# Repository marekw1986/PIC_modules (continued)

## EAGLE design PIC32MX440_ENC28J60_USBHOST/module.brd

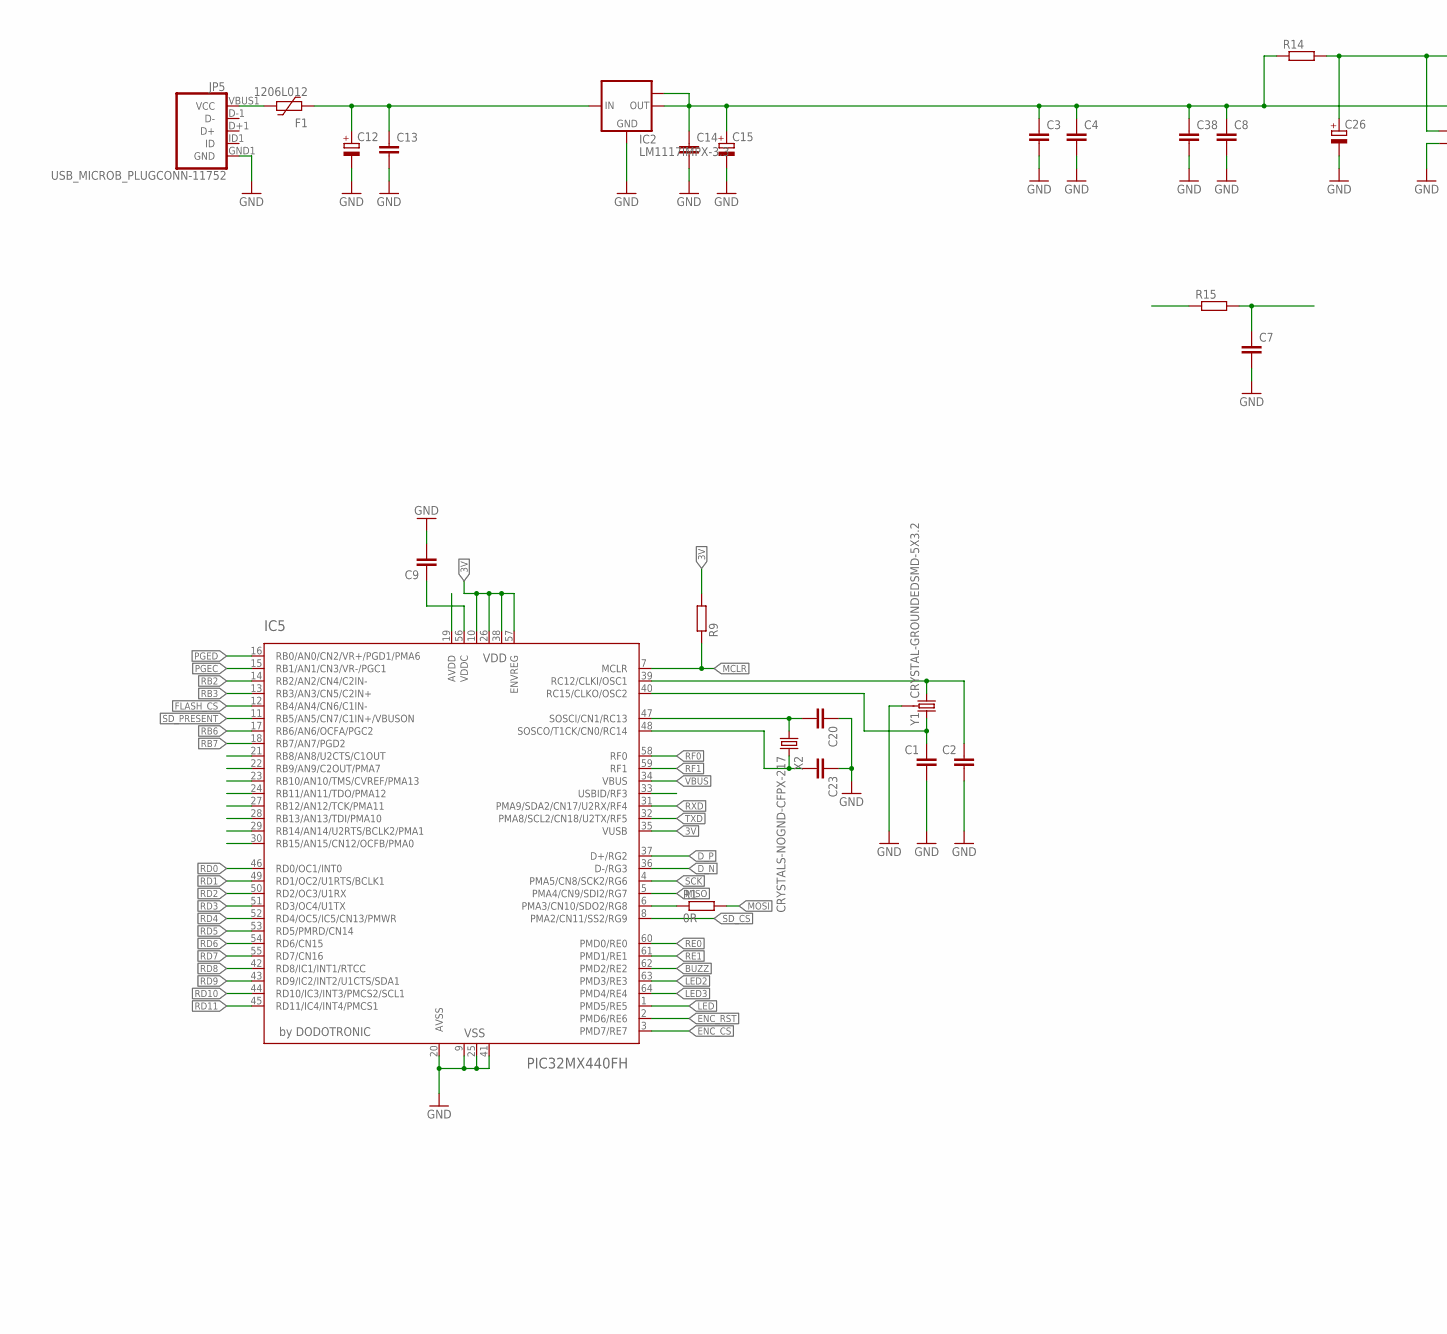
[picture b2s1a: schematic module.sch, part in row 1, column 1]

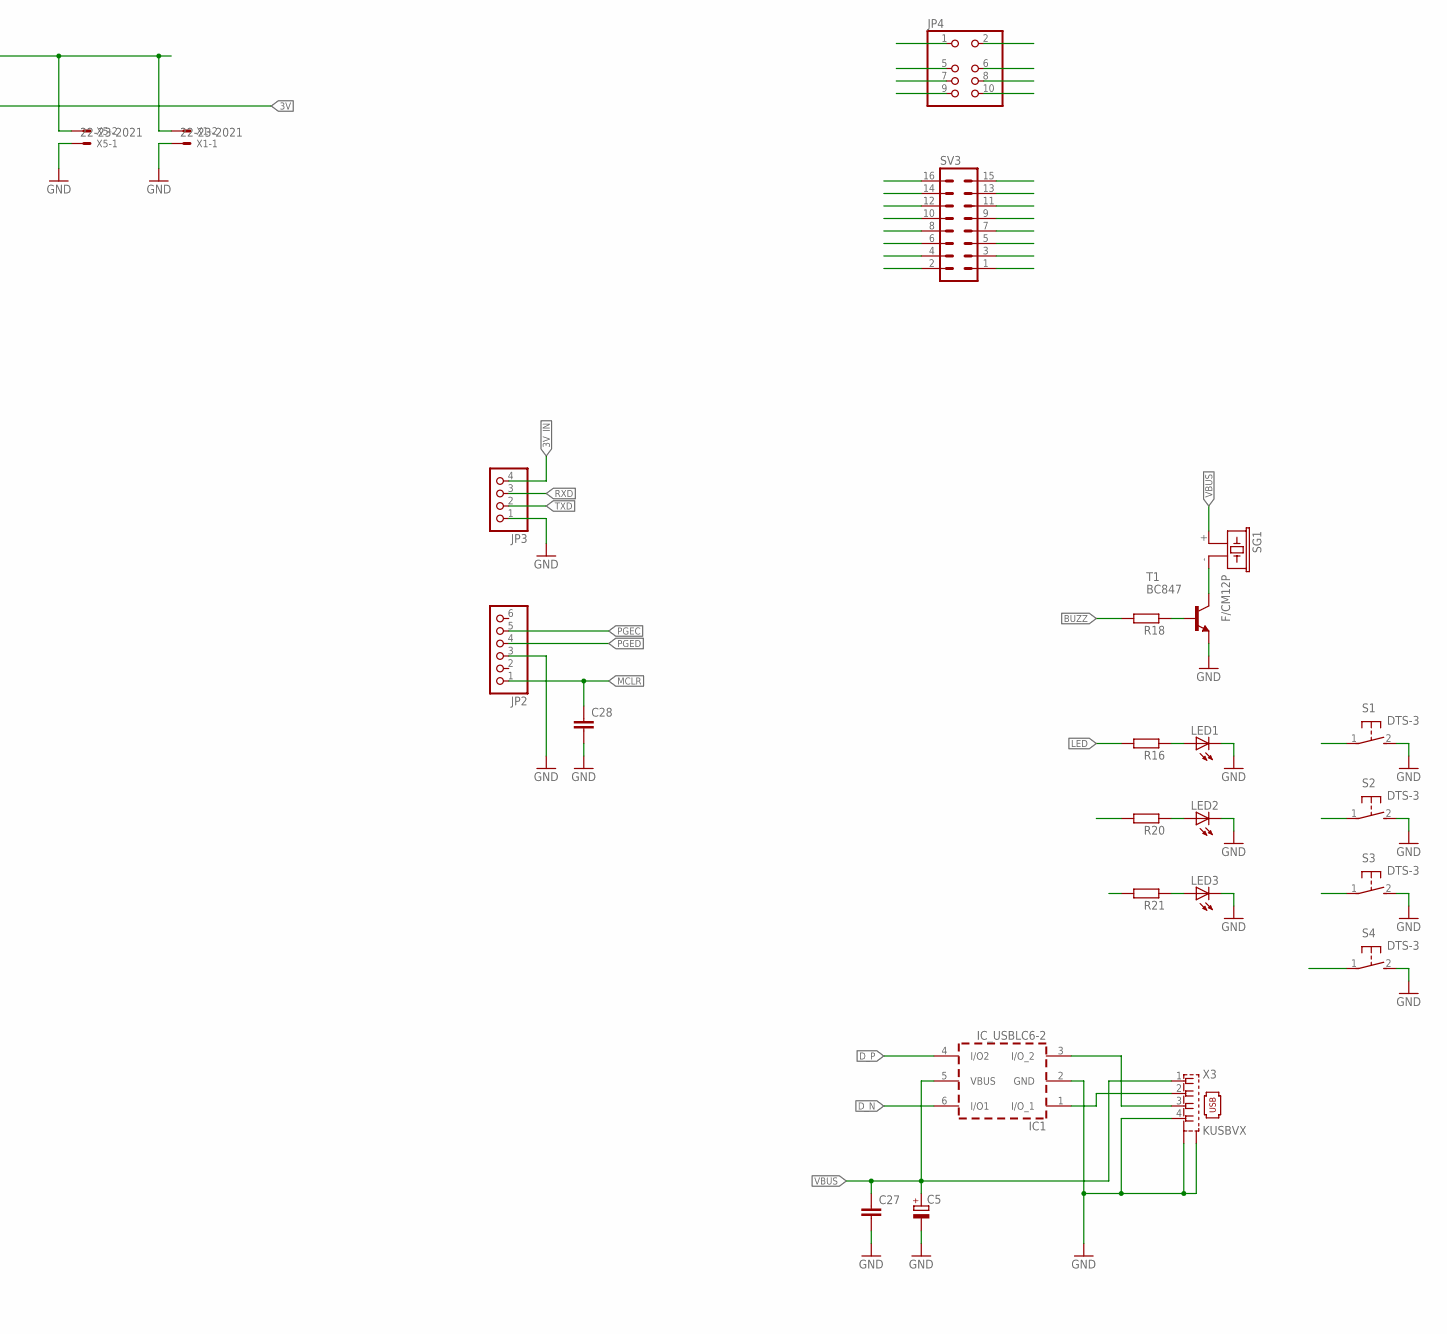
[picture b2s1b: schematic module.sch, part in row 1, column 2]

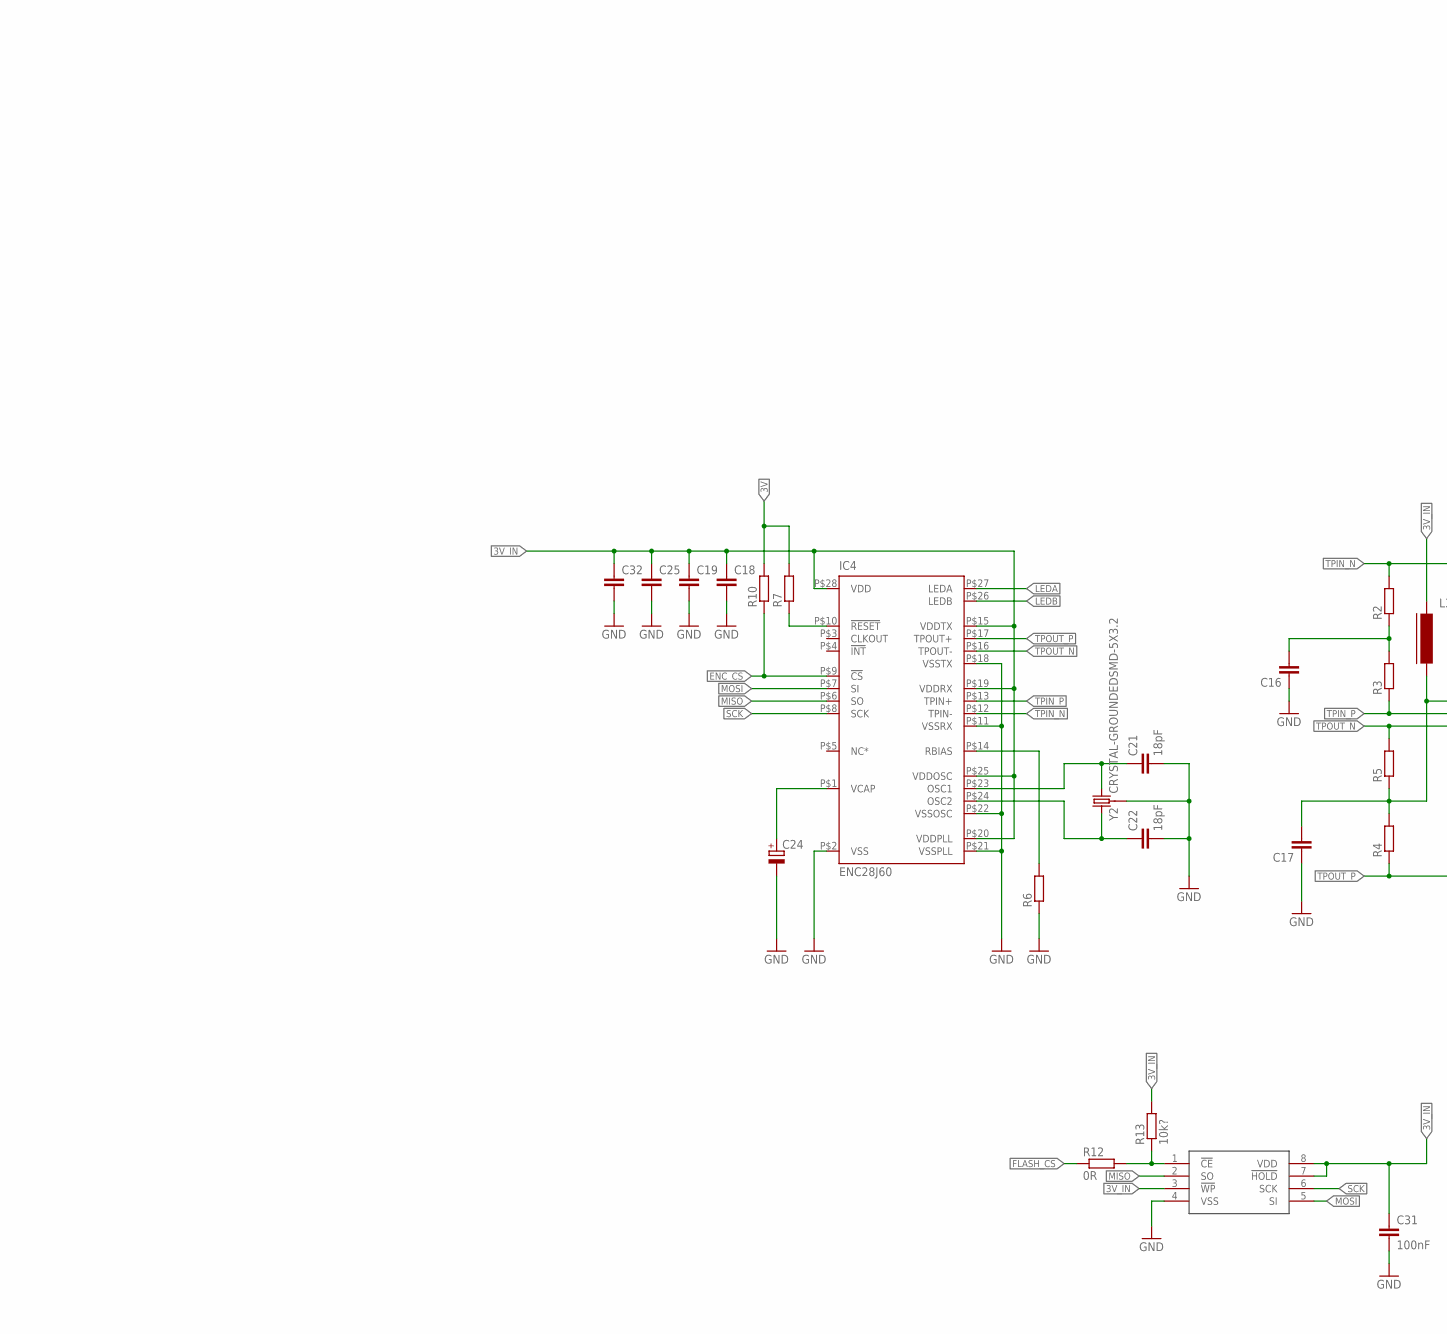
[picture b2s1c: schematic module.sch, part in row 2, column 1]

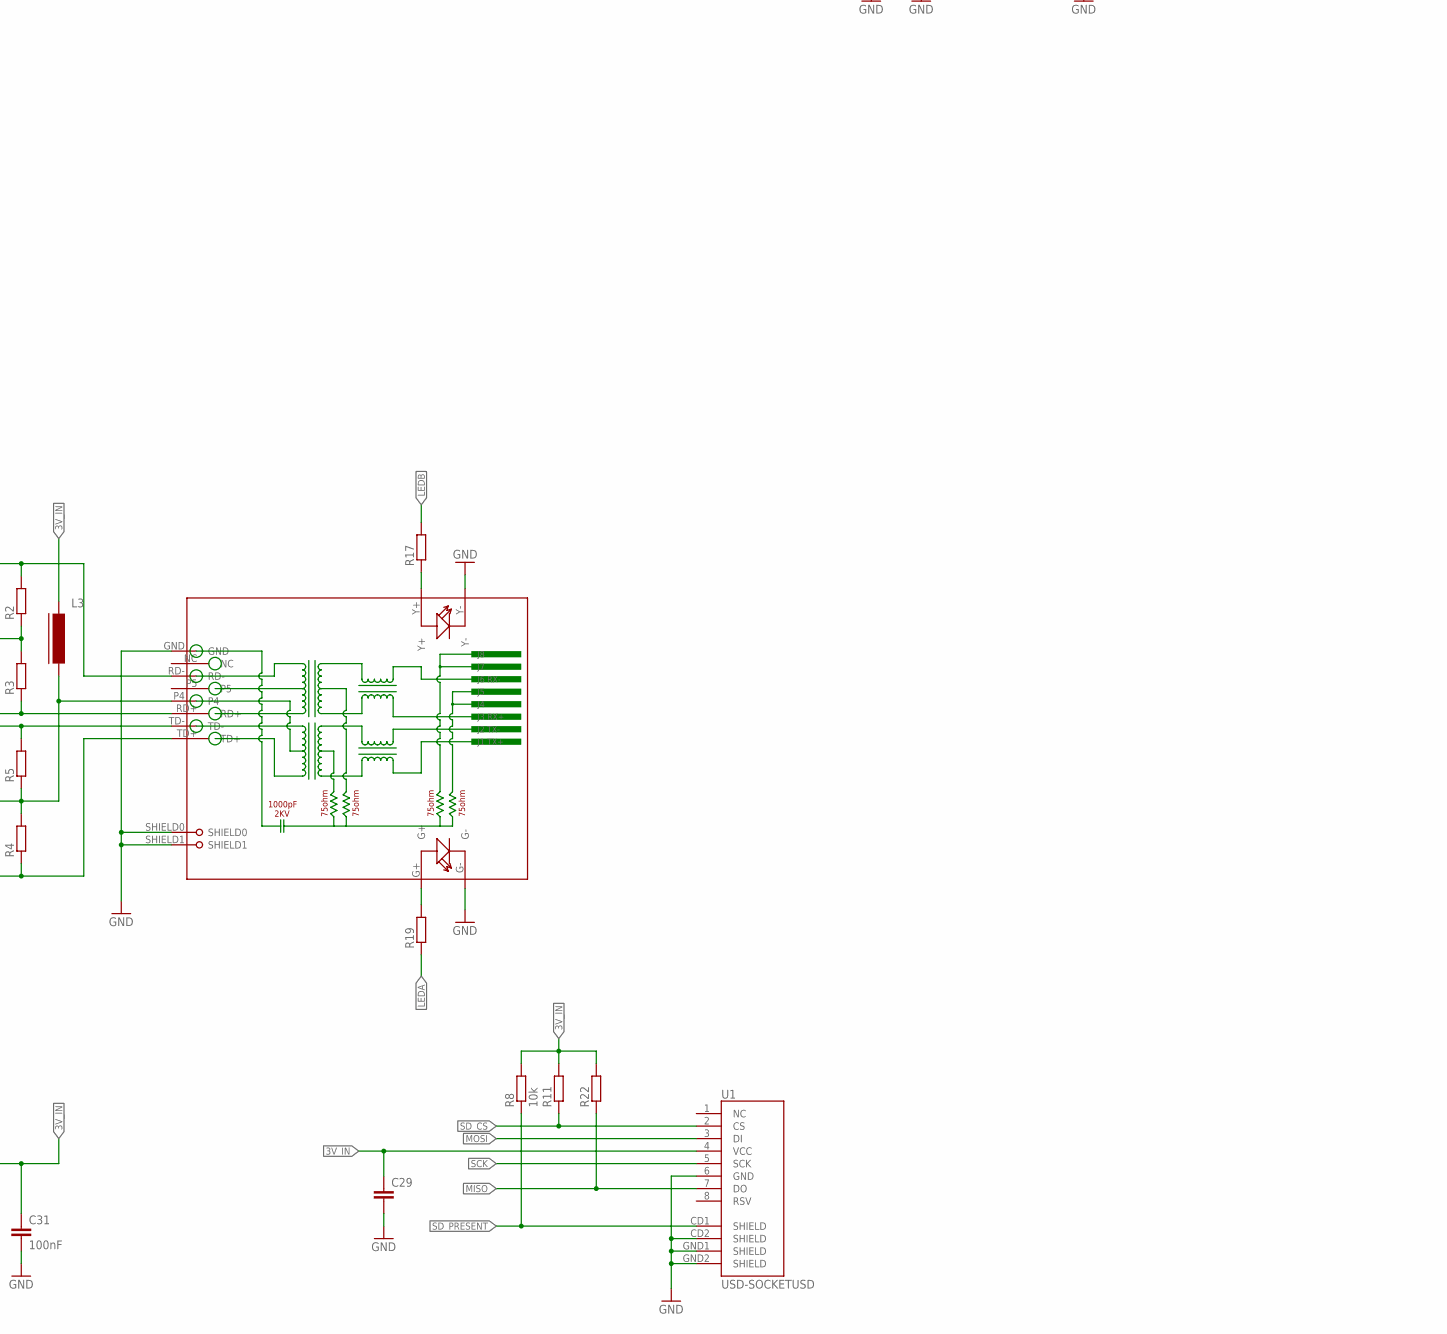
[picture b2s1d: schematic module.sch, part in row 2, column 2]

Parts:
C1, C2, C9, C13, C14, C16, C17, C19, C20, C23, C25, C27, C28, C29, C38: C-EUC0603; C0603
C3, C4, C7, C8, C18, C32: C-EUC0402; C0402
C5, C24, C26: CPOL-EUSMCA; SMC_A
C12, C15: CPOL-EUSMCB; SMC_B
C21, C22: 18pF; C0603
C31: 100nF; C0603
F1: 1206L012; 1206L
IC1: IC_USBLC6-2; SOT-23-6L
IC2: LM1117IMPX-3.3; SOT223
IC4: ENC28J60; TSSOP28W
IC5: PIC32MX440FH; TQFP64-10X10
JP2: PINHD-1X6; 1X06
JP3: PINHD-1X4; 1X04
JP4: PINHD-2X5; 2X05
JP5: USB_MICROB_PLUGCONN-11752; USB-B-MICRO-SMD_V03
L3: FERRITE-0805; FB805
LED1, LED2, LED3: LED3MM
R1, R12: 0R; R0603
R2, R3, R4, R5, R9, R10, R11, R16, R18, R20, R21, R22: R-EU_R0603; R0603
R6, R15: R-EU_R0805; R0805
R7: R-EU_R0402; R0402
R8: 10k; R0603
R13: 10k?; R0603
R14: R-EU_R2010; R2010
R17, R19: R-EU_R1206; R1206
RJ1: HR911105A
S1, S2, S3, S4: DTS-3
SG1: F/CM12P
SV3: ML16L
T1: BC847; SOT23
U1: USD-SOCKETUSD; USD-SOCKET-PP
U$2: SST25VF016BSO8M; SO-08M
X1, X5: 22-23-2021
X2: CRYSTALS-NOGND-CFPX-217; 3.2X1.5-2-PAD
X3: KUSBVX
Y1, Y2: CRYSTAL-GROUNDEDSMD-5X3.2; CRYSTAL-SMD-5X3.2-4PAD

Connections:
3V: C3.1, C4.1, C8.1, C14.1, C15.+, C38.1, IC2.2 (OUT), IC2.TAB (OUT1), IC5.10 (VDD), IC5.26 (VDD), IC5.35 (VUSB), IC5.38 (VDD), IC5.57 (ENVREG), R7.2, R9.2, R10.2, R14.1
3V_IN: C18.1, C19.1, C25.1, C26.+, C29.1, C31.1, C32.1, IC4.P$15 (VDDTX), IC4.P$19 (VDDRX), IC4.P$20 (VDDPLL), IC4.P$25 (VDDOSC), IC4.P$28 (VDD), JP3.4, L3.1, R8.2, R11.2, R13.2, R14.2, R15.1, R22.2, U1.4 (VCC), U$2.3 (!WP), U$2.7 (!HOLD), U$2.8 (VDD), X1.2, X5.2
AV_3V: C7.1, IC5.19 (AVDD), R15.2
BUZZ: IC5.62 (PMD2/RE2), R18.2
CE1: R12.2, R13.1, U$2.1 (!CE)
D2_N: IC1.1 (I/O_1), X3.2
D2_P: IC1.3 (I/O_2), X3.3
D_N: IC1.6 (I/O1), IC5.36 (D-/RG3)
D_P: IC1.4 (I/O2), IC5.37 (D+/RG2)
ENC_CS: IC4.P$9 (!CS), IC5.3 (PMD7/RE7), R10.1
ENC_RST: IC4.P$10 (!RESET), IC5.2 (PMD6/RE6), R7.1
FLASH_CS: IC5.12 (RB4/AN4/CN6/C1IN-), R12.1
GND: C1.2, C2.2, C3.2, C4.2, C5.-, C7.2, C8.2, C9.2, C12.-, C13.2, C14.2, C15.-, C16.1, C17.1, C18.2, C19.2, C20.1, C21.2, C22.2, C23.1, C24.-, C25.2, C26.-, C27.2, C28.2, C29.2, C31.2, C32.2, C38.2, IC1.2 (GND), IC2.1 (GND), IC4.P$2 (VSS), IC4.P$11 (VSSRX), IC4.P$18 (VSSTX), IC4.P$21 (VSSPLL), IC4.P$22 (VSSOSC), IC5.9 (VSS), IC5.20 (AVSS), IC5.25 (VSS), IC5.41 (VSS), JP2.3, JP3.1, JP5.GND1 (GND), LED1.K (C), LED2.K (C), LED3.K (C), R6.1, RJ1.G-, RJ1.GND, RJ1.SHIELD0, RJ1.SHIELD1, RJ1.Y-, S1.2, S2.2, S3.2, S4.2, T1.2 (E), U1.6 (GND), U1.CD2 (SHIELD), U1.GND1 (SHIELD), U1.GND2 (SHIELD), U$2.4 (VSS), X1.1, X3.4, X3.M1 (S1), X3.M2 (S2), X5.1, Y1.2 (3), Y1.4 (3), Y2.2 (3), Y2.4 (3)
LED: IC5.1 (PMD5/RE5), R16.2
LED2: IC5.63 (PMD3/RE3), R20.2
LED3: IC5.64 (PMD4/RE4), R21.2
LEDA: IC4.P$27 (LEDA), R19.1
LEDB: IC4.P$26 (LEDB), R17.2
MCLR: C28.1, IC5.7 (MCLR), JP2.1, R9.1
MISO: IC4.P$6 (SO), IC5.5 (PMA4/CN9/SDI2/RG7), R22.1, U1.7 (DO), U$2.2 (SO)
MOSI: IC4.P$7 (SI), R1.2, U1.3 (DI), U$2.5 (SI)
unnamed: SG1.- (2), T1.3 (C)
unnamed: C16.2, R2.1, R3.2
unnamed: R18.1, T1.1 (B)
unnamed: LED1.A, R16.1
unnamed: IC5.6 (PMA3/CN10/SDO2/RG8), R1.1
unnamed: C17.2, L3.2, R4.2, R5.1, RJ1.P4
unnamed: LED2.A, R20.1
unnamed: IC4.P$14 (RBIAS), R6.2
unnamed: LED3.A, R21.1
unnamed: IC5.21 (RB8/AN8/U2CTS/C1OUT), JP4.9
unnamed: IC5.22 (RB9/AN9/C2OUT/PMA7), JP4.10
unnamed: IC5.23 (RB10/AN10/TMS/CVREF/PMA13), JP4.7
unnamed: F1.1, JP5.VBUS1 (VCC)
unnamed: IC5.24 (RB11/AN11/TDO/PMA12), JP4.8
unnamed: IC5.28 (RB13/AN13/TDI/PMA10), JP4.5
unnamed: IC5.29 (RB14/AN14/U2RTS/BCLK2/PMA1), JP4.6
unnamed: C21.1, IC4.P$23 (OSC1), Y2.1 (2)
unnamed: C22.1, IC4.P$24 (OSC2), Y2.3 (1)
unnamed: IC5.30 (RB15/AN15/CN12/OCFB/PMA0), JP4.1
unnamed: IC5.33 (USBID/RF3), JP4.2
unnamed: C24.+, IC4.P$1 (VCAP)
unnamed: R17.1, RJ1.Y+
unnamed: R19.2, RJ1.G+
OSC1: C2.1, IC5.39 (RC12/CLKI/OSC1), Y1.1 (2)
OSC2: C1.1, IC5.40 (RC15/CLKO/OSC2), Y1.3 (1)
PGEC: IC5.15 (RB1/AN1/CN3/VR-/PGC1), JP2.5
PGED: IC5.16 (RB0/AN0/CN2/VR+/PGD1/PMA6), JP2.4
RB2: IC5.14 (RB2/AN2/CN4/C2IN-), S2.1
RB3: IC5.13 (RB3/AN3/CN5/C2IN+), S1.1
RB6: IC5.17 (RB6/AN6/OCFA/PGC2), S3.1
RB7: IC5.18 (RB7/AN7/PGD2), S4.1
RD0: IC5.46 (RD0/OC1/INT0), SV3.6
RD1: IC5.49 (RD1/OC2/U1RTS/BCLK1), SV3.5
RD2: IC5.50 (RD2/OC3/U1RX), SV3.8
RD3: IC5.51 (RD3/OC4/U1TX), SV3.7
RD4: IC5.52 (RD4/OC5/IC5/CN13/PMWR), SV3.10
RD5: IC5.53 (RD5/PMRD/CN14), SV3.9
RD6: IC5.54 (RD6/CN15), SV3.12
RD7: IC5.55 (RD7/CN16), SV3.11
RD8: IC5.42 (RD8/IC1/INT1/RTCC), SV3.2
RD9: IC5.43 (RD9/IC2/INT2/U1CTS/SDA1), SV3.1
RD10: IC5.44 (RD10/IC3/INT3/PMCS2/SCL1), SV3.4
RD11: IC5.45 (RD11/IC4/INT4/PMCS1), SV3.3
RE0: IC5.60 (PMD0/RE0), SV3.16
RE1: IC5.61 (PMD1/RE1), SV3.15
RF0: IC5.58 (RF0), SV3.14
RF1: IC5.59 (RF1), SV3.13
RXD: IC5.31 (PMA9/SDA2/CN17/U2RX/RF4), JP3.3
SCK: IC4.P$8 (SCK), IC5.4 (PMA5/CN8/SCK2/RG6), U1.5 (SCK), U$2.6 (SCK)
SD_CS: IC5.8 (PMA2/CN11/SS2/RG9), R11.1, U1.2 (CS)
SD_PRESENT: IC5.11 (RB5/AN5/CN7/C1IN+/VBUSON), R8.1, U1.CD1 (SHIELD)
SOSCI: C20.2, IC5.47 (SOSCI/CN1/RC13), X2.1
SOSCO: C23.2, IC5.48 (SOSCO/T1CK/CN0/RC14), X2.2
TPIN_N: IC4.P$12 (TPIN-), R2.2, RJ1.RD-
TPIN_P: IC4.P$13 (TPIN+), R3.1, RJ1.RD+
TPOUT_N: IC4.P$16 (TPOUT-), R5.2, RJ1.TD-
TPOUT_P: IC4.P$17 (TPOUT+), R4.1, RJ1.TD+
TXD: IC5.32 (PMA8/SCL2/CN18/U2TX/RF5), JP3.2
VBUS: C5.+, C12.+, C13.1, C27.1, F1.2, IC1.5 (VBUS), IC2.3 (IN), IC5.34 (VBUS), SG1.+ (1), X3.1
VCAP: C9.1, IC5.56 (VDDC)

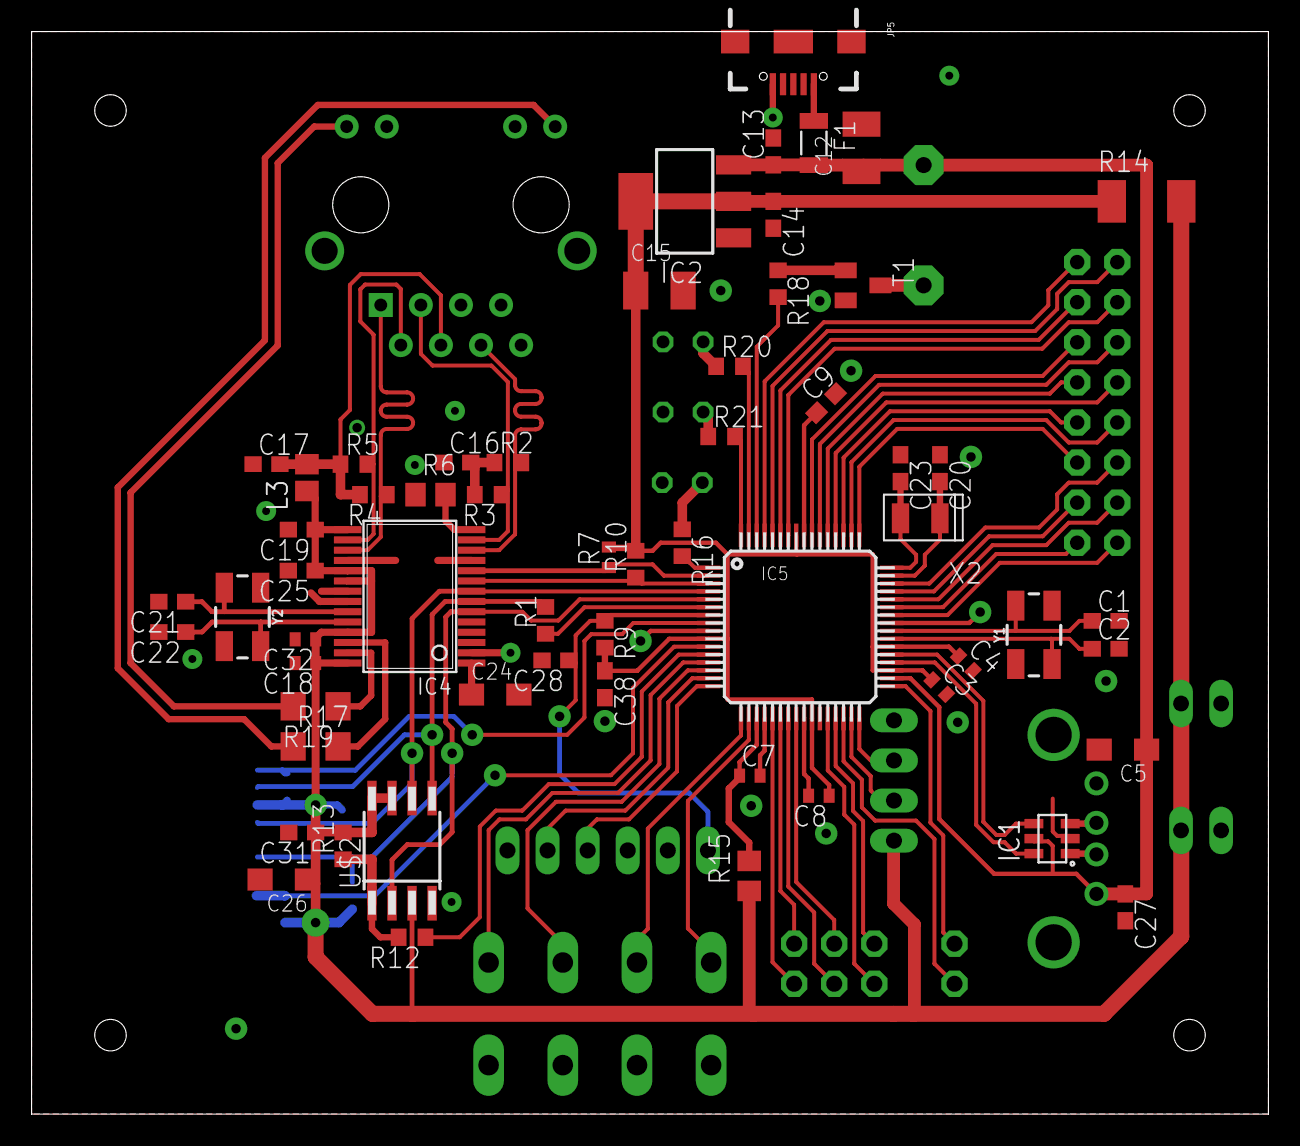
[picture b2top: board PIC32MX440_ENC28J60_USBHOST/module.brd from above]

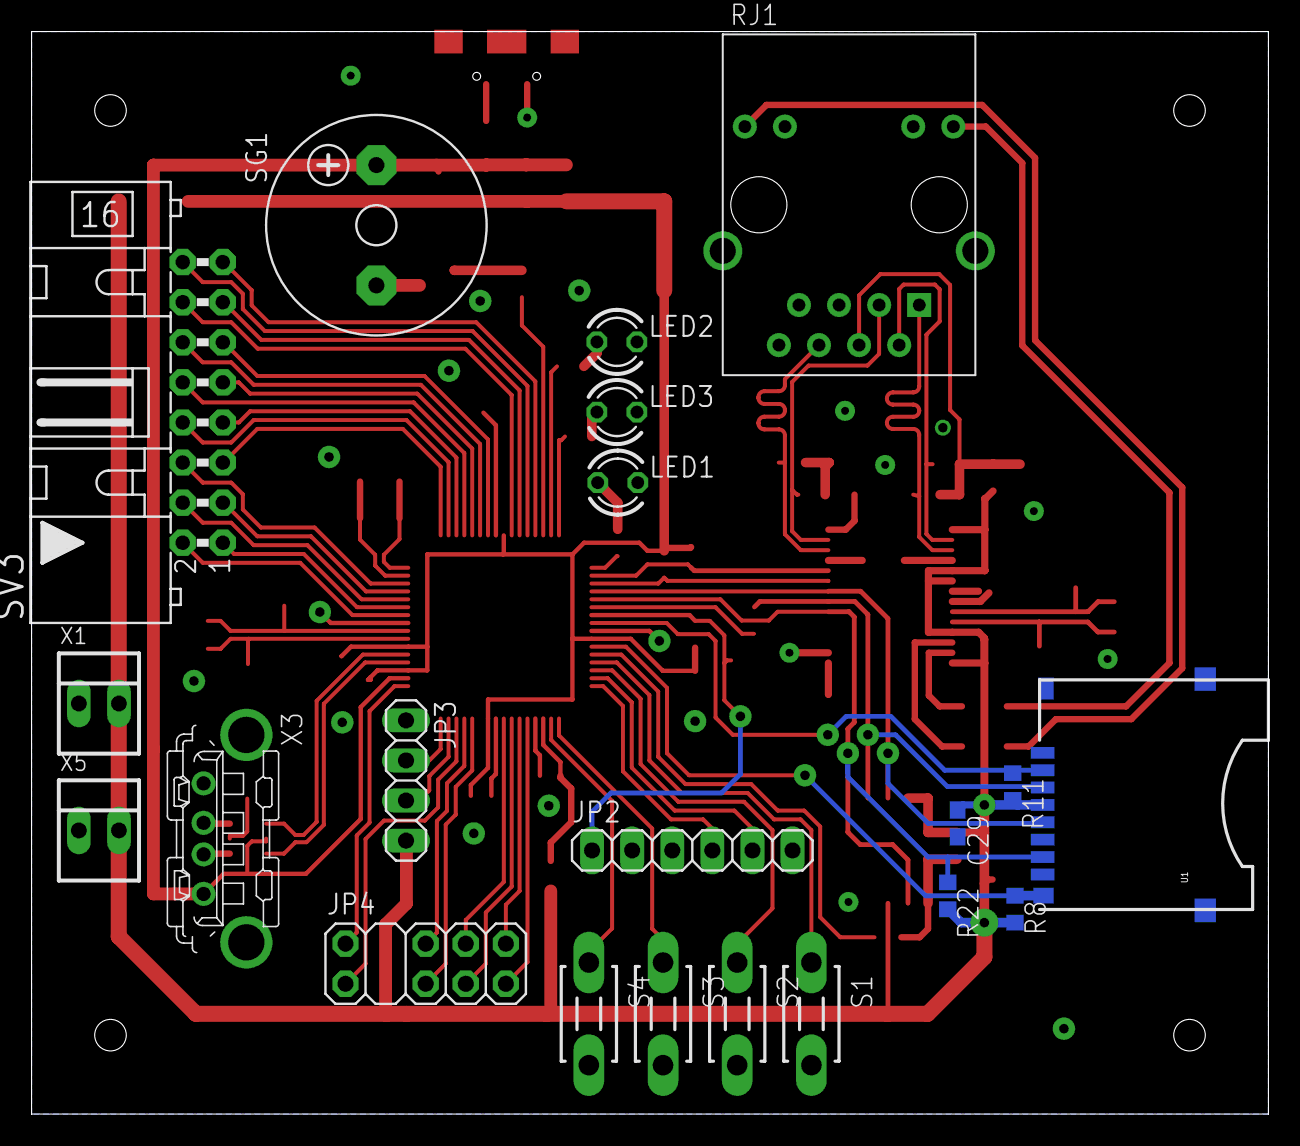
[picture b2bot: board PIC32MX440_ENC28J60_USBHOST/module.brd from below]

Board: 2 copper layers, 78.4 x 68.6 mm, 80 parts (21 on the bottom side), 81 nets.
